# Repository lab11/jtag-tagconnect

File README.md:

JTAG to Tag Connect
===================

This PCB is an adapter that converts the [20 pin JLink](https://www.segger.com/jlink-debug-probes.html) connector to
a [6-pin Tag Connect](http://www.tag-connect.com/TC2030-IDC-NL),
much like [this](https://www.segger.com/jlink-6-pin-adapter.html) board.
Ours, however, additionally contains an onboard LDO
that can supply 3.3V to the attached device and the VTRef pin on the J-Link programmer
so that it can program boards that are not self powered.

Interface
---------

- **Switch 1**, labeled `VREF`: Set to `3V3` to connect the `VCC` pin on the TagConnect
header (and the attached board to be programmed) and the `VTRef` pin from
the Segger JLink to the 3.3 V output from the regulator.
Set to `DEV` to directly connect the `VTRef` pin on the JLink to the TagConnect
VCC pin. This sets the I/O voltage for the JLink, but does not power the target board.

- **Switch 2**, labeled `SWDIO`: This switch can connect the `SWDIO` and
`!RESET` signals, which is needed on some ICs. To leave the signals
disconnected, leave the switch in the empty (down) position.

Troubleshooting
---------------

1. Blue LED does not come on when attached to JLink.
You need to enable the 5 V output on the JLink:

        $ JlinkExe
        power on perm

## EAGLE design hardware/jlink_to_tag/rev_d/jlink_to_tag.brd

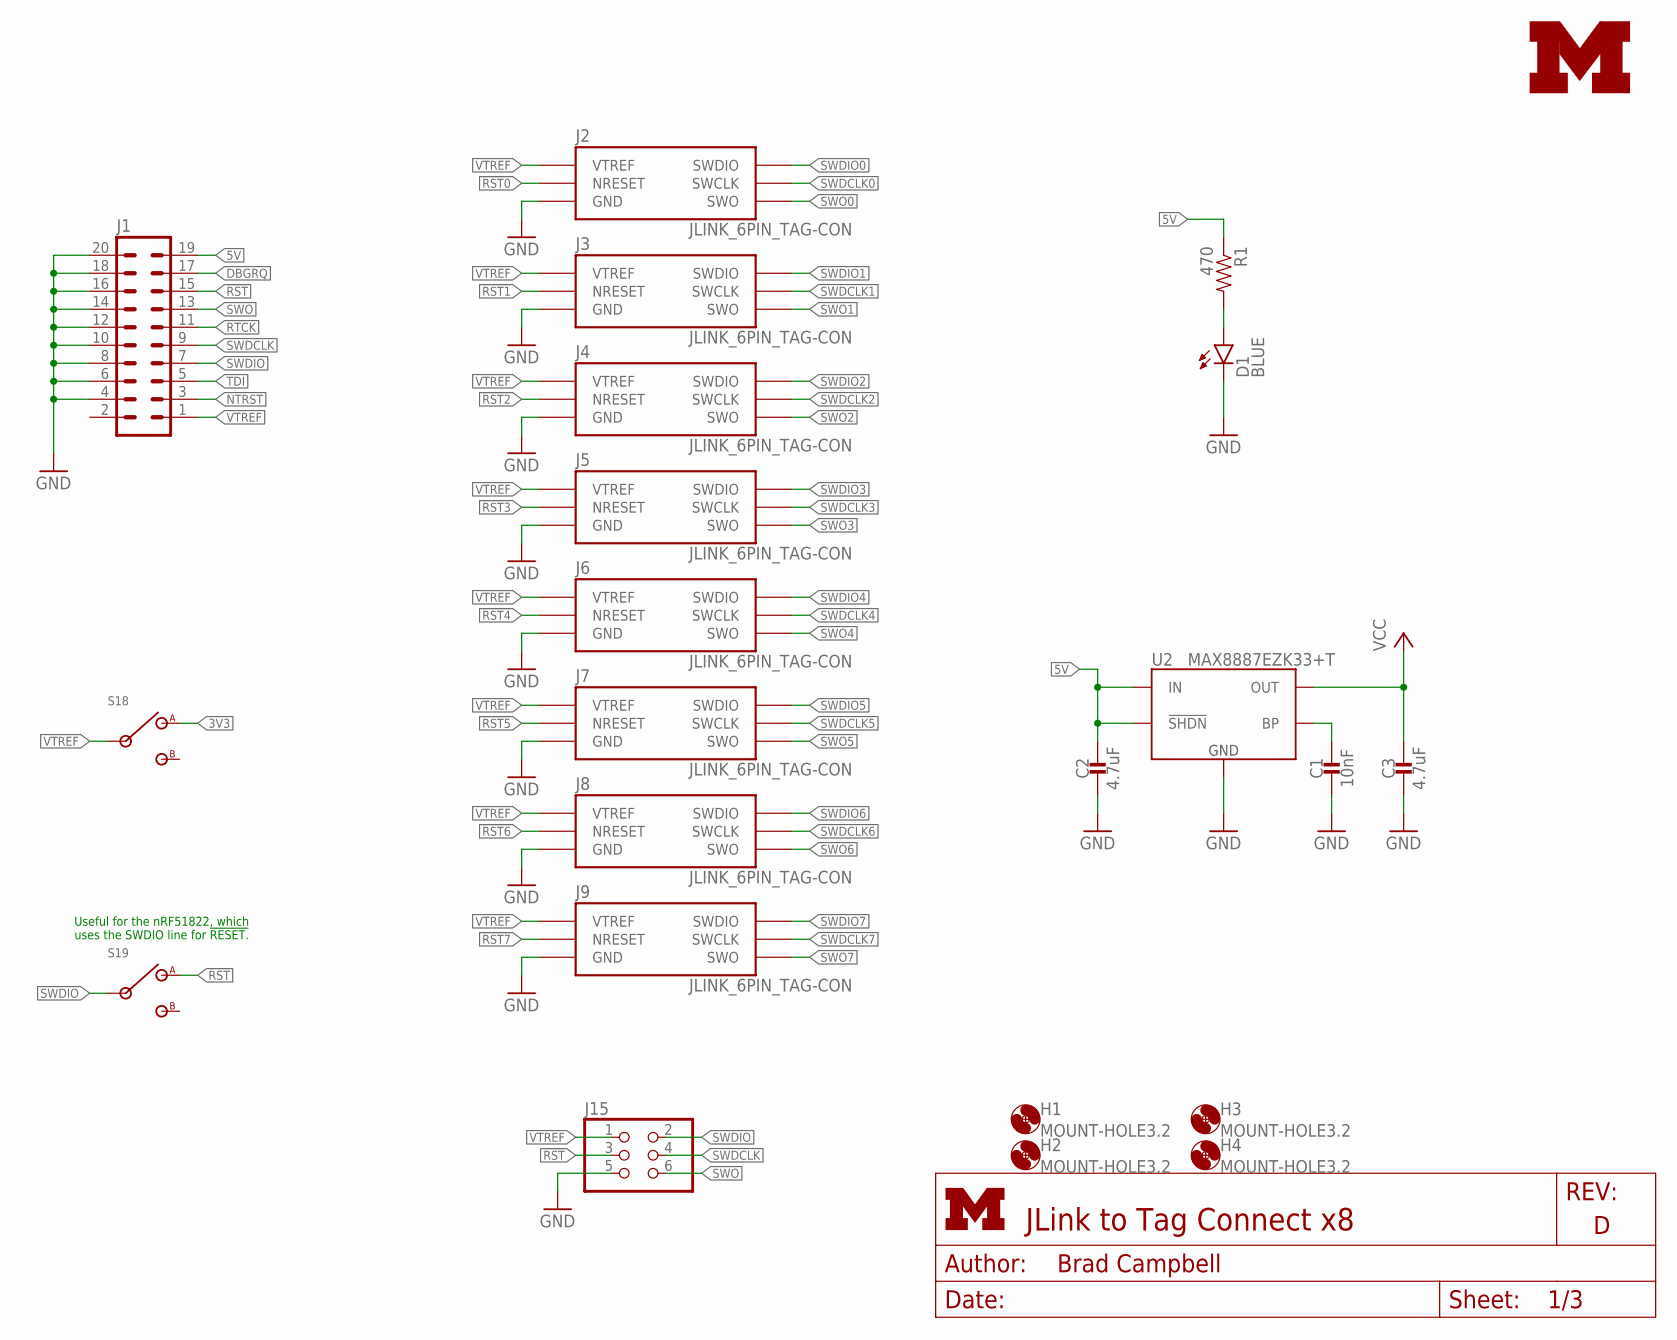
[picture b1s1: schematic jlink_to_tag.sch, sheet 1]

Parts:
C1: 10nF; 0603_CAP; DIGIKEY 490-1512-1-ND
C2, C3: 4.7uF; 0603_CAP; DIGIKEY 490-3297-1-ND
D1: BLUE; LED-0603
H1, H2, H3, H4: MOUNT-HOLE3.2; 3,2
J1: ML20; DIGIKEY S9172-ND
J2, J3, J4, J5, J6, J7, J8, J9: JLINK_6PIN_TAG-CON; 2X3_MALE_SHROUDED_0.100
J15: PINHD-2X3; 2X03
LOGO1: UMICH_SOLID_SMALL+; UMICH_SOLID_100MIL
R1: 470; 0603-RES
S18, S19: STS121PC04
U2: MAX8887EZK33+T; SOT-23-5

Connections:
3V3: C3.1, S18.1, U2.5 (OUT); also elsewhere on the board
5V: C2.1, J1.19, R1.1, U2.1 (IN), U2.3 (!SHDN)
!RST: J1.15, J15.3, S19.1; also elsewhere on the board
!RST0: J2.3 (NRESET); also elsewhere on the board
!RST1: J3.3 (NRESET); also elsewhere on the board
!RST2: J4.3 (NRESET); also elsewhere on the board
!RST3: J5.3 (NRESET); also elsewhere on the board
!RST4: J6.3 (NRESET); also elsewhere on the board
!RST5: J7.3 (NRESET); also elsewhere on the board
!RST6: J8.3 (NRESET); also elsewhere on the board
!RST7: J9.3 (NRESET); also elsewhere on the board
DBGRQ: J1.17
GND: C1.2, C2.2, C3.2, D1.C, J1.4, J1.6, J1.8, J1.10, J1.12, J1.14, J1.16, J1.18, J1.20, J2.5 (GND), J3.5 (GND), J4.5 (GND), J5.5 (GND), J6.5 (GND), J7.5 (GND), J8.5 (GND), J9.5 (GND), J15.5, U2.2 (GND); also elsewhere on the board
unnamed: C1.1, U2.4 (BP)
unnamed: D1.A, R1.2
NTRST: J1.3
RTCK: J1.11
SWDCLK: J1.9, J15.4; also elsewhere on the board
SWDCLK0: J2.4 (SWCLK); also elsewhere on the board
SWDCLK1: J3.4 (SWCLK); also elsewhere on the board
SWDCLK2: J4.4 (SWCLK); also elsewhere on the board
SWDCLK3: J5.4 (SWCLK); also elsewhere on the board
SWDCLK4: J6.4 (SWCLK); also elsewhere on the board
SWDCLK5: J7.4 (SWCLK); also elsewhere on the board
SWDCLK6: J8.4 (SWCLK); also elsewhere on the board
SWDCLK7: J9.4 (SWCLK); also elsewhere on the board
SWDIO: J1.7, J15.2, S19.2; also elsewhere on the board
SWDIO0: J2.2 (SWDIO); also elsewhere on the board
SWDIO1: J3.2 (SWDIO); also elsewhere on the board
SWDIO2: J4.2 (SWDIO); also elsewhere on the board
SWDIO3: J5.2 (SWDIO); also elsewhere on the board
SWDIO4: J6.2 (SWDIO); also elsewhere on the board
SWDIO5: J7.2 (SWDIO); also elsewhere on the board
SWDIO6: J8.2 (SWDIO); also elsewhere on the board
SWDIO7: J9.2 (SWDIO); also elsewhere on the board
SWO: J1.13, J15.6; also elsewhere on the board
SWO0: J2.6 (SWO); also elsewhere on the board
SWO1: J3.6 (SWO); also elsewhere on the board
SWO2: J4.6 (SWO); also elsewhere on the board
SWO3: J5.6 (SWO); also elsewhere on the board
SWO4: J6.6 (SWO); also elsewhere on the board
SWO5: J7.6 (SWO); also elsewhere on the board
SWO6: J8.6 (SWO); also elsewhere on the board
SWO7: J9.6 (SWO); also elsewhere on the board
TDI: J1.5
VTREF: J1.1, J2.1 (VTREF), J3.1 (VTREF), J4.1 (VTREF), J5.1 (VTREF), J6.1 (VTREF), J7.1 (VTREF), J8.1 (VTREF), J9.1 (VTREF), J15.1, S18.2

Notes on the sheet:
Useful for the nRF51822, which uses the SWDIO line for !RESET.

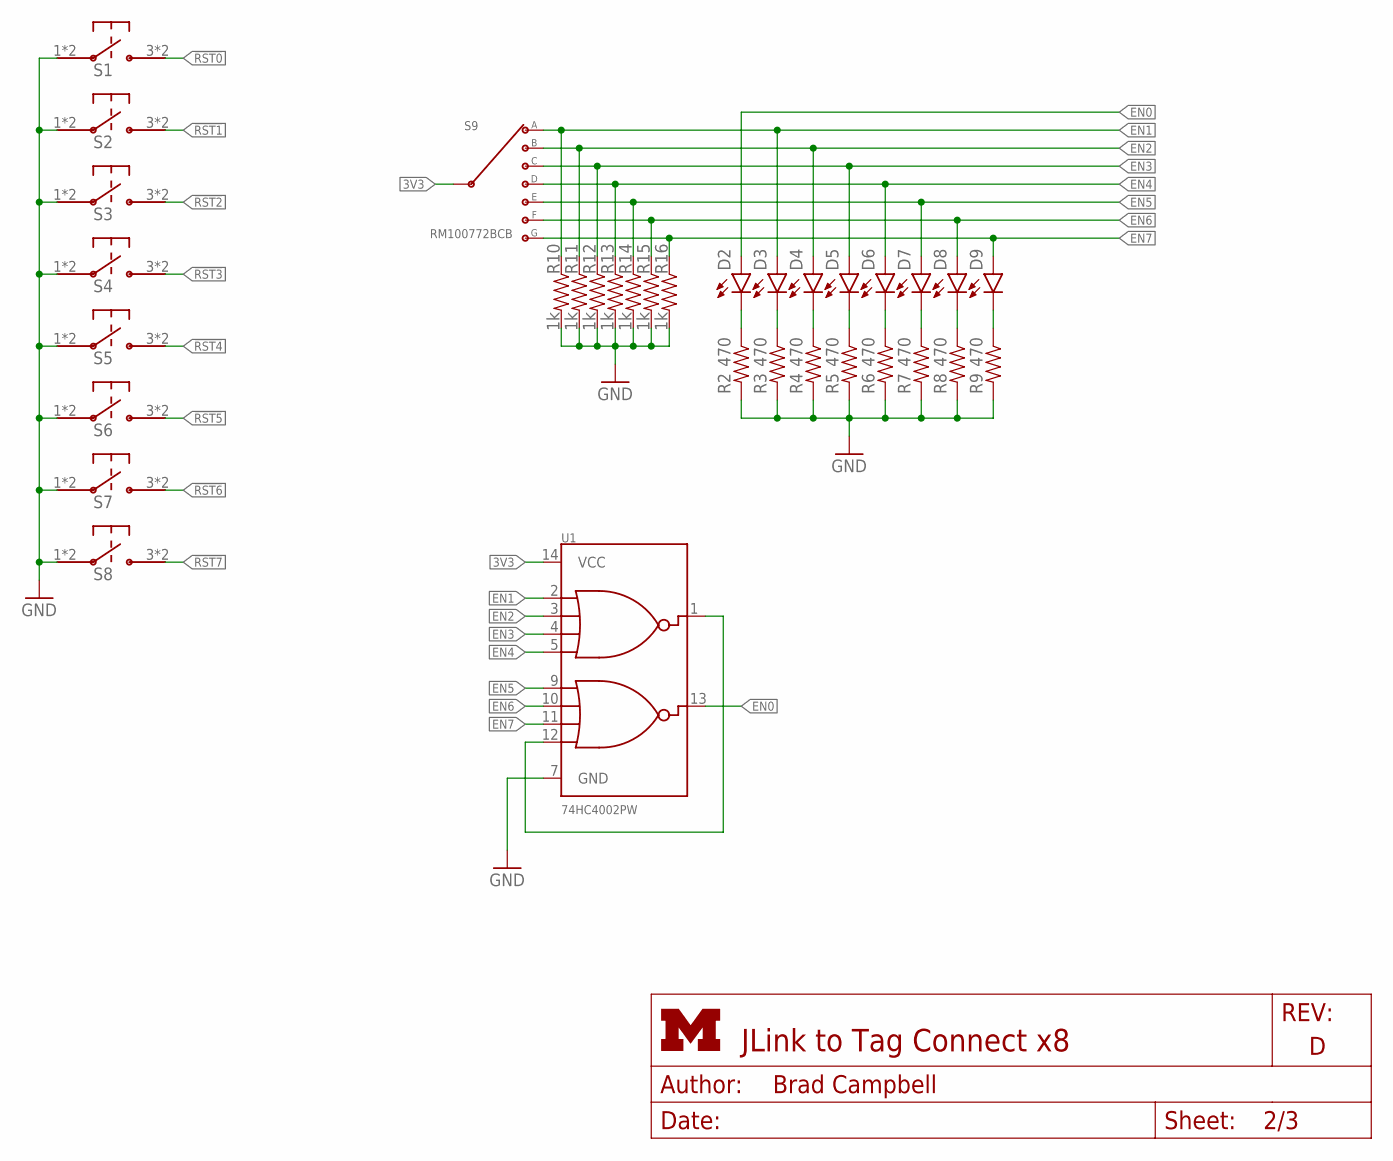
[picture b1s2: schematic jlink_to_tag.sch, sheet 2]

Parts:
D2, D3, D4, D5, D6, D7, D8, D9: BLUE; LED-0603
R2, R3, R4, R5, R6, R7, R8, R9: 470; 0603-RES
R10, R11, R12, R13, R14, R15, R16: 1k; 0603-RES
S1, S2, S3, S4, S5, S6, S7, S8: PTS645SM43SMTR92; PTS645
S9: RM100772BCB; RM-SWITCH
U1: 74HC4002PW; TSSOP-14/5MM

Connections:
3V3: S9.C (INPUT), U1.14 (VCC); also elsewhere on the board
!RST0: S1.3, S1.4; also elsewhere on the board
!RST1: S2.3, S2.4; also elsewhere on the board
!RST2: S3.3, S3.4; also elsewhere on the board
!RST3: S4.3, S4.4; also elsewhere on the board
!RST4: S5.3, S5.4; also elsewhere on the board
!RST5: S6.3, S6.4; also elsewhere on the board
!RST6: S7.3, S7.4; also elsewhere on the board
!RST7: S8.3, S8.4; also elsewhere on the board
EN0: D2.A, U1.13 (BOUT); also elsewhere on the board
EN1: D3.A, R10.1, S9.1 (A), U1.2 (A1); also elsewhere on the board
EN2: D4.A, R11.1, S9.2 (B), U1.3 (A2); also elsewhere on the board
EN3: D5.A, R12.1, S9.3 (C), U1.4 (A3); also elsewhere on the board
EN4: D6.A, R13.1, S9.4 (D), U1.5 (A4); also elsewhere on the board
EN5: D7.A, R14.1, S9.5 (E), U1.9 (B1); also elsewhere on the board
EN6: D8.A, R15.1, S9.6 (F), U1.10 (B2); also elsewhere on the board
EN7: D9.A, R16.1, S9.7 (G), U1.11 (B3); also elsewhere on the board
GND: R2.2, R3.2, R4.2, R5.2, R6.2, R7.2, R8.2, R9.2, R10.2, R11.2, R12.2, R13.2, R14.2, R15.2, R16.2, S1.1, S1.2, S2.1, S2.2, S3.1, S3.2, S4.1, S4.2, S5.1, S5.2, S6.1, S6.2, S7.1, S7.2, S8.1, S8.2, U1.7 (GND); also elsewhere on the board
unnamed: D2.C, R2.1
unnamed: D3.C, R3.1
unnamed: D4.C, R4.1
unnamed: D5.C, R5.1
unnamed: D6.C, R6.1
unnamed: D7.C, R7.1
unnamed: D8.C, R8.1
unnamed: D9.C, R9.1
unnamed: U1.1 (AOUT), U1.12 (B4)

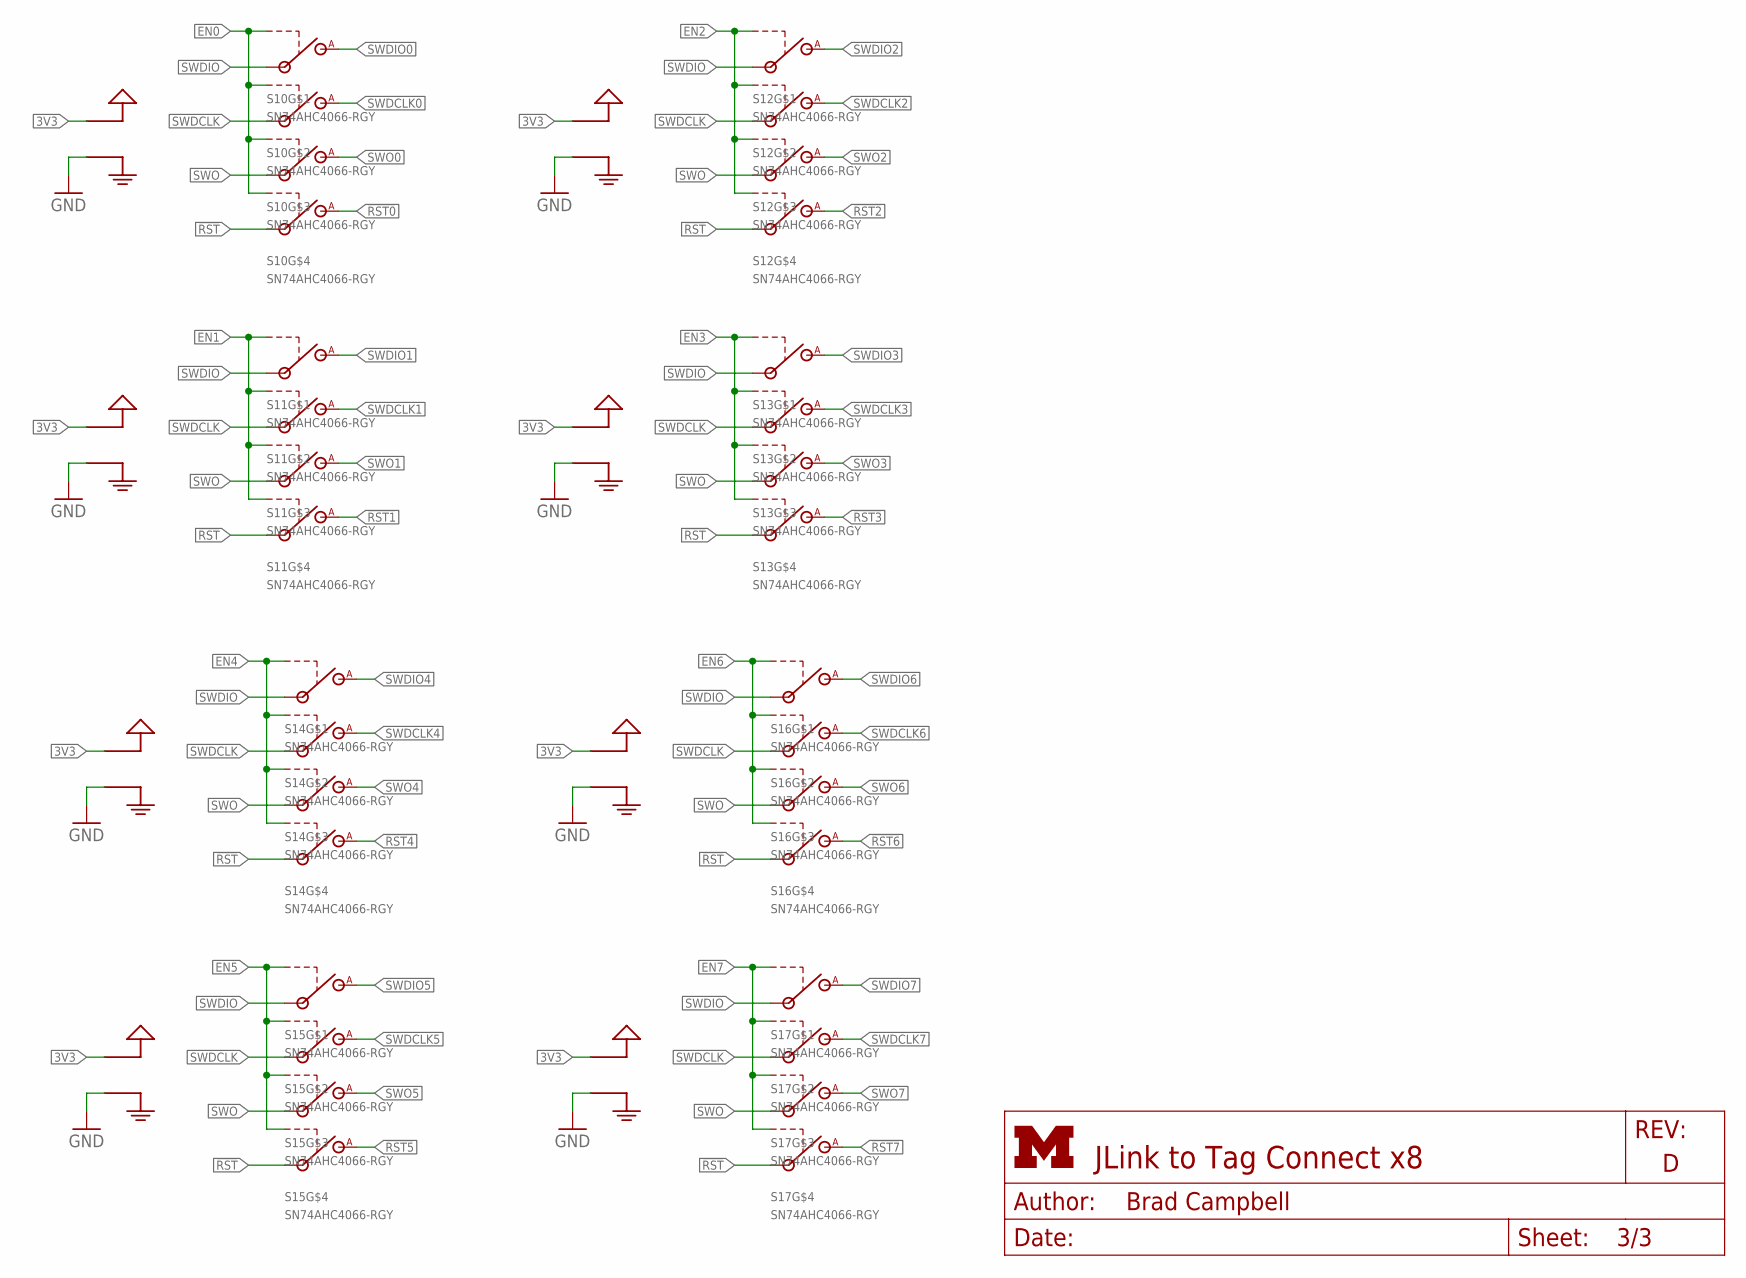
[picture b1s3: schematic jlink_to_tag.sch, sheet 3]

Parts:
S10, S11, S12, S13, S14, S15, S16, S17: SN74AHC4066-RGY; S-PVQFN-N14-3.5MM

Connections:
3V3: S10.14 (VCC), S11.14 (VCC), S12.14 (VCC), S13.14 (VCC), S14.14 (VCC), S15.14 (VCC), S16.14 (VCC), S17.14 (VCC); also elsewhere on the board
!RST: S10.11 (IN), S11.11 (IN), S12.11 (IN), S13.11 (IN), S14.11 (IN), S15.11 (IN), S16.11 (IN), S17.11 (IN); also elsewhere on the board
!RST0: S10.10 (A); also elsewhere on the board
!RST1: S11.10 (A); also elsewhere on the board
!RST2: S12.10 (A); also elsewhere on the board
!RST3: S13.10 (A); also elsewhere on the board
!RST4: S14.10 (A); also elsewhere on the board
!RST5: S15.10 (A); also elsewhere on the board
!RST6: S16.10 (A); also elsewhere on the board
!RST7: S17.10 (A); also elsewhere on the board
EN0: S10.5 (CTRL), S10.6 (CTRL), S10.12 (CTRL), S10.13 (CTRL); also elsewhere on the board
EN1: S11.5 (CTRL), S11.6 (CTRL), S11.12 (CTRL), S11.13 (CTRL); also elsewhere on the board
EN2: S12.5 (CTRL), S12.6 (CTRL), S12.12 (CTRL), S12.13 (CTRL); also elsewhere on the board
EN3: S13.5 (CTRL), S13.6 (CTRL), S13.12 (CTRL), S13.13 (CTRL); also elsewhere on the board
EN4: S14.5 (CTRL), S14.6 (CTRL), S14.12 (CTRL), S14.13 (CTRL); also elsewhere on the board
EN5: S15.5 (CTRL), S15.6 (CTRL), S15.12 (CTRL), S15.13 (CTRL); also elsewhere on the board
EN6: S16.5 (CTRL), S16.6 (CTRL), S16.12 (CTRL), S16.13 (CTRL); also elsewhere on the board
EN7: S17.5 (CTRL), S17.6 (CTRL), S17.12 (CTRL), S17.13 (CTRL); also elsewhere on the board
GND: S10.7 (GND), S11.7 (GND), S12.7 (GND), S13.7 (GND), S14.7 (GND), S15.7 (GND), S16.7 (GND), S17.7 (GND); also elsewhere on the board
SWDCLK: S10.4 (IN), S11.4 (IN), S12.4 (IN), S13.4 (IN), S14.4 (IN), S15.4 (IN), S16.4 (IN), S17.4 (IN); also elsewhere on the board
SWDCLK0: S10.3 (A); also elsewhere on the board
SWDCLK1: S11.3 (A); also elsewhere on the board
SWDCLK2: S12.3 (A); also elsewhere on the board
SWDCLK3: S13.3 (A); also elsewhere on the board
SWDCLK4: S14.3 (A); also elsewhere on the board
SWDCLK5: S15.3 (A); also elsewhere on the board
SWDCLK6: S16.3 (A); also elsewhere on the board
SWDCLK7: S17.3 (A); also elsewhere on the board
SWDIO: S10.1 (IN), S11.1 (IN), S12.1 (IN), S13.1 (IN), S14.1 (IN), S15.1 (IN), S16.1 (IN), S17.1 (IN); also elsewhere on the board
SWDIO0: S10.2 (A); also elsewhere on the board
SWDIO1: S11.2 (A); also elsewhere on the board
SWDIO2: S12.2 (A); also elsewhere on the board
SWDIO3: S13.2 (A); also elsewhere on the board
SWDIO4: S14.2 (A); also elsewhere on the board
SWDIO5: S15.2 (A); also elsewhere on the board
SWDIO6: S16.2 (A); also elsewhere on the board
SWDIO7: S17.2 (A); also elsewhere on the board
SWO: S10.8 (IN), S11.8 (IN), S12.8 (IN), S13.8 (IN), S14.8 (IN), S15.8 (IN), S16.8 (IN), S17.8 (IN); also elsewhere on the board
SWO0: S10.9 (A); also elsewhere on the board
SWO1: S11.9 (A); also elsewhere on the board
SWO2: S12.9 (A); also elsewhere on the board
SWO3: S13.9 (A); also elsewhere on the board
SWO4: S14.9 (A); also elsewhere on the board
SWO5: S15.9 (A); also elsewhere on the board
SWO6: S16.9 (A); also elsewhere on the board
SWO7: S17.9 (A); also elsewhere on the board

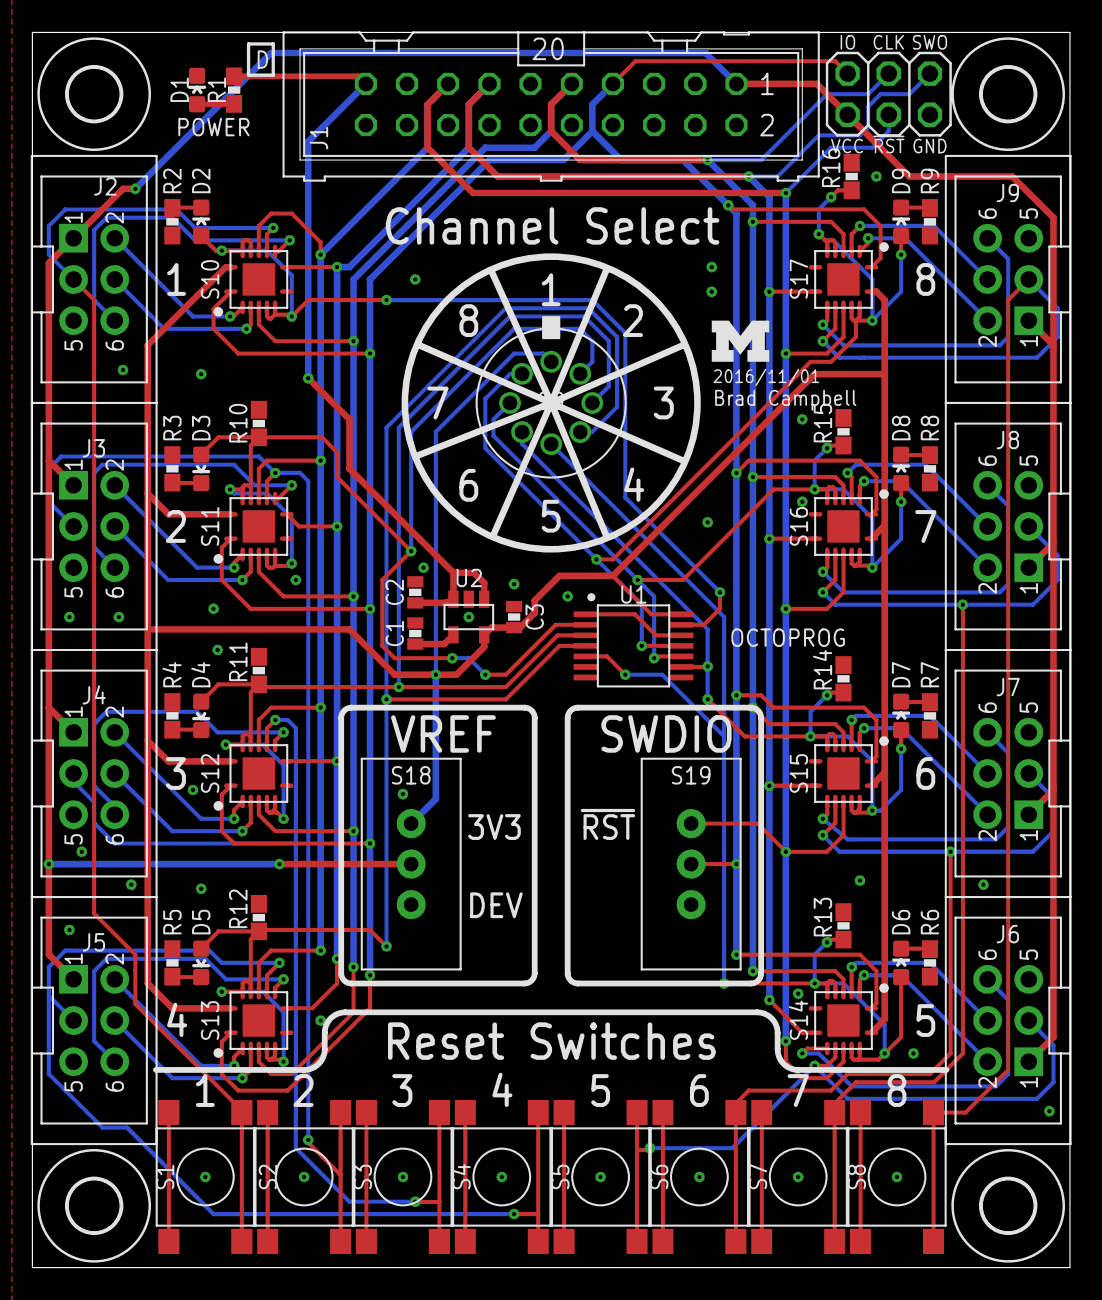
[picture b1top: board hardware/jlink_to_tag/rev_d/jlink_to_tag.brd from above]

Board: 2 copper layers, 64.0 x 76.2 mm, 64 parts (0 on the bottom side), 59 nets.

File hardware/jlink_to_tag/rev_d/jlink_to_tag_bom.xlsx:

Qty | Value | Device | Package | Parts | Description | DIGIKEY
1 | 10nF | CAPACITOR0603_CAP | 0603_CAP | C1 | 0402 Capacitor | 490-1512-1-ND
2 | 4.7uF | CAPACITOR0603_CAP | 0603_CAP | C2, C3 | 0402 Capacitor | 490-3297-1-ND
9 | BLUE | LED-BLUE0603 | LED-0603 | D1, D2, D3, D4, D5, D6, D7, D8, D9 | Blue LEDs
1 |  | ML20 | ML20 | J1 | HARTING | S9172-ND
8 | JLINK_6PIN_TAG-CON | JLINK_6PIN_TAG-CON | 2X3_MALE_SHROUDED_0.100 | J2, J3, J4, J5, J6, J7, J8, J9 | This is a 6-pin Tag Connect header with the J-Link. | 3M15451-ND
1 |  | PINHD-2X3 | 2X03 | J10 | PIN HEADER
9 | 470 | RESISTOR0603-RES | 0603-RES | R1, R2, R3, R4, R5, R6, R7, R8, R9 | Resistor
7 | 1k | RESISTOR0603-RES | 0603-RES | R10, R11, R12, R13, R14, R15, R16 | Resistor
8 | PTS645SM43SMTR92 | PTS645SM43SMTR92 | PTS645 | S1, S2, S3, S4, S5, S6, S7, S8 | Tactile Switch SPST-NO Top Actuated Surface Mount | CKN9112CT-ND
1 | RM100772BCB | RM100772BCB | RM-SWITCH | S9 | Rotary Switch 8 Position SP7T 500mA (DC) 24VDC Through Hole
8 | SN74AHC4066-RGY | SN74AHC4066-RGY | S-PVQFN-N14-3.5MM | S10, S11, S12, S13, S14, S15, S16, S17 |  | 296-15258-1-ND
2 | STS121PC04 | STS121PC04 | STS121PC04 | S18, S19 | Slide Switch SPDT Through Hole | 450-1609-ND
1 | 74HC4002PW | 74HC4002PW | TSSOP-14/5MM | U1 | NOR Gate IC 2 Channel 14-TSSOP | 568-8879-1-ND
1 | MAX8887EZK33+T | MAX8887EZK33+T | SOT-23-5 | U2 | IC REG LDO 3.3V 0.3A TSOT23-5 | MAX8887EZK33+TCT-ND

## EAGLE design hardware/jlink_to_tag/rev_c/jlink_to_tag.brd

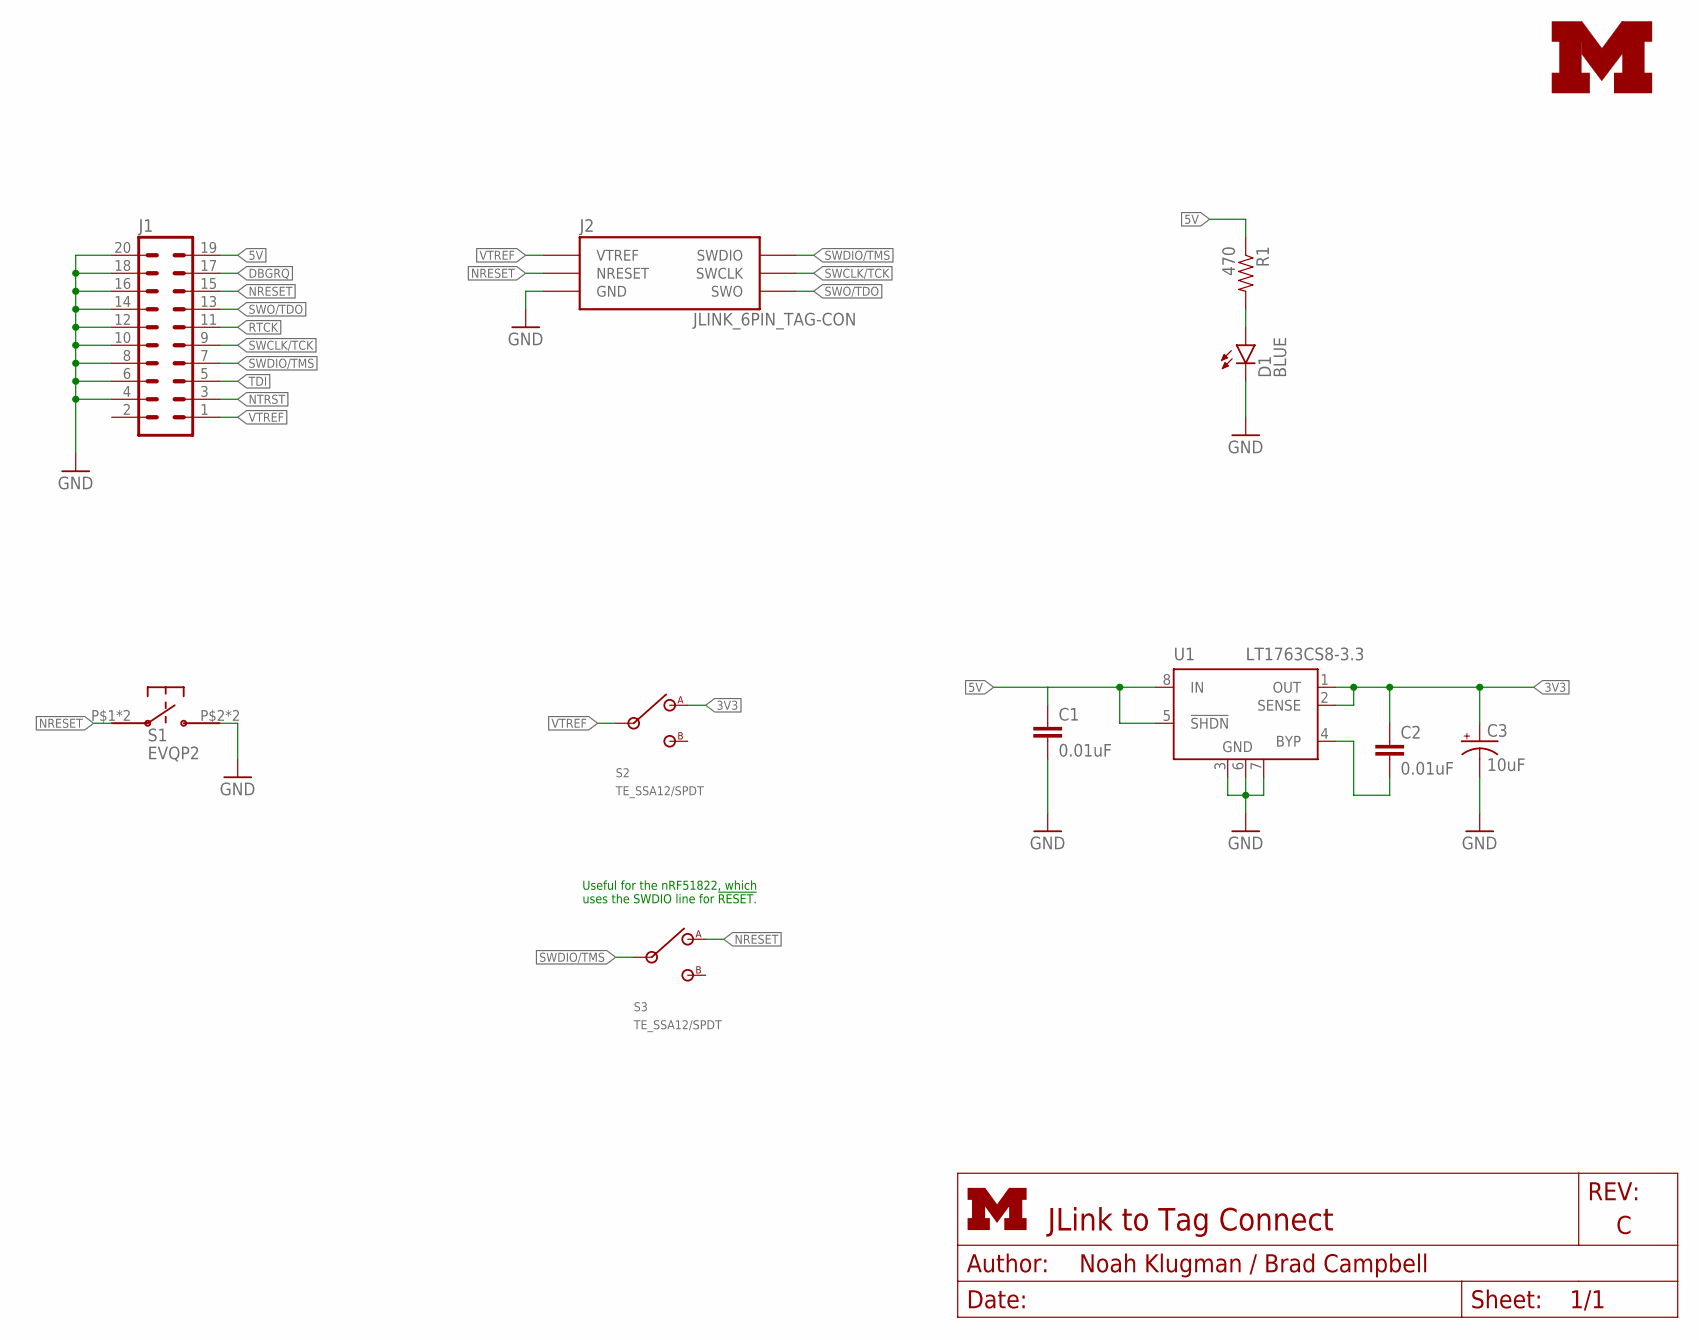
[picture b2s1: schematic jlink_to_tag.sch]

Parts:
C1, C2: 0.01uF; C0603; DIGIKEY 490-1512-1-ND
C3: 10uF; EIA3216; DIGIKEY 399-3684-1-ND
D1: BLUE; LED-0603
J1: ML20; DIGIKEY S9172-ND
J2: JLINK_6PIN_TAG-CON; 2X3_MALE_SHROUDED_0.100
LOGO1: UMICH_SOLID_SMALL+; UMICH_SOLID_100MIL
R1: 470; 0603-RES
S1: EVQP2
S2, S3: TE_SSA12/SPDT
U1: LT1763CS8-3.3; SOIC8; DIGIKEY LT1763CS8-3.3#TRPBFCT-ND

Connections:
3V3: C2.1, C3.A (+), S2.1 (A), U1.1 (OUT), U1.2 (SENSE)
5V: C1.1, J1.19, R1.1, U1.5 (!SHDN), U1.8 (IN)
DBGRQ: J1.17
GND: C1.2, C3.C (-), D1.C, J1.4, J1.6, J1.8, J1.10, J1.12, J1.14, J1.16, J1.18, J1.20, J2.5 (GND), S1.P$2, S1.P$4, U1.3 (GND), U1.6 (GND), U1.7 (GND)
unnamed: D1.A, R1.2
unnamed: C2.2, U1.4 (BYP)
NRESET: J1.15, J2.3 (NRESET), S1.P$1, S1.P$3, S3.1 (A)
NTRST: J1.3
RTCK: J1.11
SWCLK/TCK: J1.9, J2.4 (SWCLK)
SWDIO/TMS: J1.7, J2.2 (SWDIO), S3.IN
SWO/TDO: J1.13, J2.6 (SWO)
TDI: J1.5
VTREF: J1.1, J2.1 (VTREF), S2.IN

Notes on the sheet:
Useful for the nRF51822, which uses the SWDIO line for !RESET.

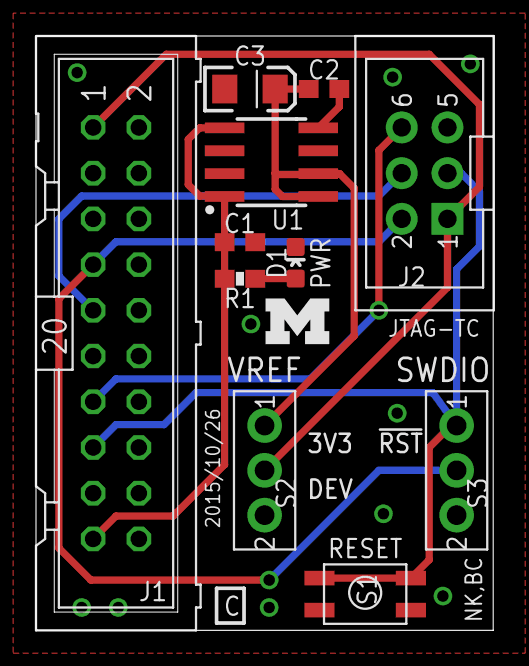
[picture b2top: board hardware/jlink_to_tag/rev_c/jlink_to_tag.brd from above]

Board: 2 copper layers, 25.4 x 33.0 mm, 12 parts (0 on the bottom side), 10 nets.

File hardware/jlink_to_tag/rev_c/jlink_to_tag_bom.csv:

# Bill of Materials
# Converted from jlink_to_tag_bom.xlsx
# Generated by bom_to_text.py

Qty,Value,Device,Package,Parts,Description,DIGIKEY
2,0.01uF,C-EUC0603,C0603,"C1, C2","CAPACITOR, European symbol",490-1512-1-ND
1,10uF,CAP_POL1206,EIA3216,C3,Capacitor Polarized,399-3684-1-ND
1,BLUE,LED-BLUE0603,LED-0603,D1,Blue LEDs for production use,
1,,ML20,ML20,J1,HARTING,S9172-ND
1,JLINK_6PIN_TAG-CON,JLINK_6PIN_TAG-CON,2X3_MALE_SHROUDED_0.100,J2,This is a 6-pin Tag Connect header with the J-Link.,3M15451-ND
1,470,RESISTOR0603-RES,0603-RES,R1,Resistor,
1,EVQP2,EVQP2,EVQP2,S1,SWITCH TACTILE SPST-NO 0.02A 15V,P11084SCT-ND
2,TE_SSA12/SPDT,TE_SSA12/SPDT,TE_SSA12/SPDT,"S2, S3",SWITCH SLIDE SPDT 2POS SSA SER,450-1602-ND
1,LT1763CS8-3.3,LT1763CS8-3.3,SOIC8,U1,"500mA, Low Noise, LDO Micropower Regulators",LT1763CS8-3.3#TRPBFCT-ND

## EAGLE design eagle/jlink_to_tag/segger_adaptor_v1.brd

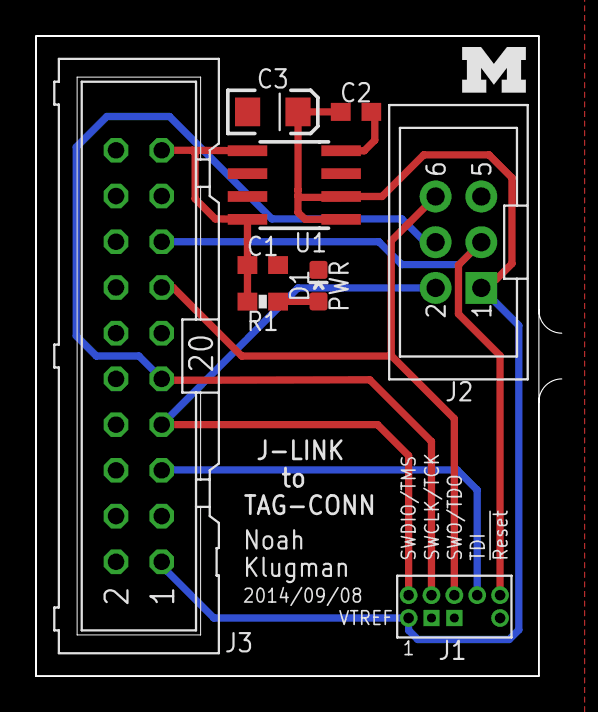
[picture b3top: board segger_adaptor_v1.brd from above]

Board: 2 copper layers, 29.2 x 35.6 mm, 10 parts (0 on the bottom side), 10 nets.

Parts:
C1, C2: 0.01uF; C0603
C3: 10uF; EIA3216
D1: BLUE; LED-0603
J1: PINHD-2X5/0.050-NO7; 2X5-0.050-NO7
J2: JLINK_6PIN_TAG-CON; 2X3_MALE_SHROUDED_0.100
J3: ML20
LOGO1: UMICH_SOLID_SMALL+; UMICH_SOLID_100MIL
R1: 470; 0603-RES
U1: LT1763CS8-3.3; SOIC8

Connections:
5V: C1.1, J3.19, R1.1, U1.5, U1.8
GND: C1.2, C3.C, D1.C, J1.GND@1, J1.GND@2, J2.5, J3.4, J3.6, J3.8, J3.10, J3.12, J3.14, J3.16, J3.18, J3.20, U1.3, U1.6, U1.7
unnamed: D1.A, R1.2
unnamed: C2.2, U1.4
NRESET: J1.NRESET, J2.3, J3.15
SWCLK/TCK: J1.SWCLK/TCK, J2.4, J3.9
SWDIO/TMS: J1.SWDIO/TMS, J2.2, J3.7
SWO/TDO: J1.SWO/TDO, J2.6, J3.13
TDI: J1.TDI, J3.5
VTREF: C2.1, C3.A, J1.VTREF, J2.1, J3.1, U1.1, U1.2

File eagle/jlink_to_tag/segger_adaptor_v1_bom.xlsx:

Qty | Value | Device | Package | Parts | Description | DIGIKEY
2 | 0.01uF | C-EUC0603 | C0603 | C1, C2 | CAPACITOR, European symbol | 490-1512-1-ND
1 | 10uF | CAP_POL1206 | EIA3216 | C3 | Capacitor Polarized | 399-3684-1-ND
1 | BLUE | LED-BLUE0603 | LED-0603 | D1 | Blue LEDs for production use
1 | PINHD-2X5/0.050-NO7 | PINHD-2X5/0.050-NO7 | 2X5-0.050-NO7 | J1 |  | 609-3712-ND
1 | JLINK_6PIN_TAG-CON | JLINK_6PIN_TAG-CON | 2X3_MALE_SHROUDED_0.100 | J2 | This is a 6-pin Tag Connect header with the J-Link. | 3M15451-ND
1 |  | ML20 | ML20 | J3 | HARTING | S9172-ND
1 | 470 | RESISTOR0603-RES | 0603-RES | R1 | Resistor
1 | LT1763CS8-3.3 | LT1763CS8-3.3 | SOIC8 | U1 | 500mA, Low Noise, LDO Micropower Regulators | LT1763CS8-3.3#TRPBFCT-ND

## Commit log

2014-09-08 adding in the segger board
2014-09-08 readme
2014-09-08 oops... wrong boards...
2014-09-08 updates to adapter board
2014-09-08 added .cool
2014-09-08 added docs for board
2015-02-11 update folder structure
2015-02-11 rev b of jlink to tag connect
    new:
    - switch to select if you want to use the regulator or let the
    device set vtref
    - reset button
2015-02-11 changed silkscreen
2015-02-11 improve readme
2015-03-22 added notes
2015-06-11 bug fixes to rev b
2015-09-05 tag connect board
2015-10-24 added rev c with new switch
    can now toggle between version that works for nrf and for other arm
    chips
2015-10-24 update readme
    this board works for more than just nrf chips
2015-10-24 revert rev b to the version that was fabbed
2015-10-24 1x1.3 inches
2015-10-26 add output for jtag to tagconnect rev c
2016-06-16 more notes on how to use the adapter
2016-10-31 jlink TIMES 8!!
2016-11-01 getting more traces in
2016-11-02 board layout
2016-11-09 started renumber rev d
2016-11-09 Order switches
2016-11-09 add bom
2016-11-09 octoprog
2016-11-11 added zips
2021-02-04 add some more logos; round the corners
2021-02-05 lower logo resolutions for CAM

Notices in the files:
parts and their libraries:
SparkFun-Passives: Licensing: Creative Commons ShareAlike 4.0 International - https://creativecommons.org/licenses/by-sa/4.0
